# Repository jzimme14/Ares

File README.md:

# Ares
Flight Controller for autonomous drone.

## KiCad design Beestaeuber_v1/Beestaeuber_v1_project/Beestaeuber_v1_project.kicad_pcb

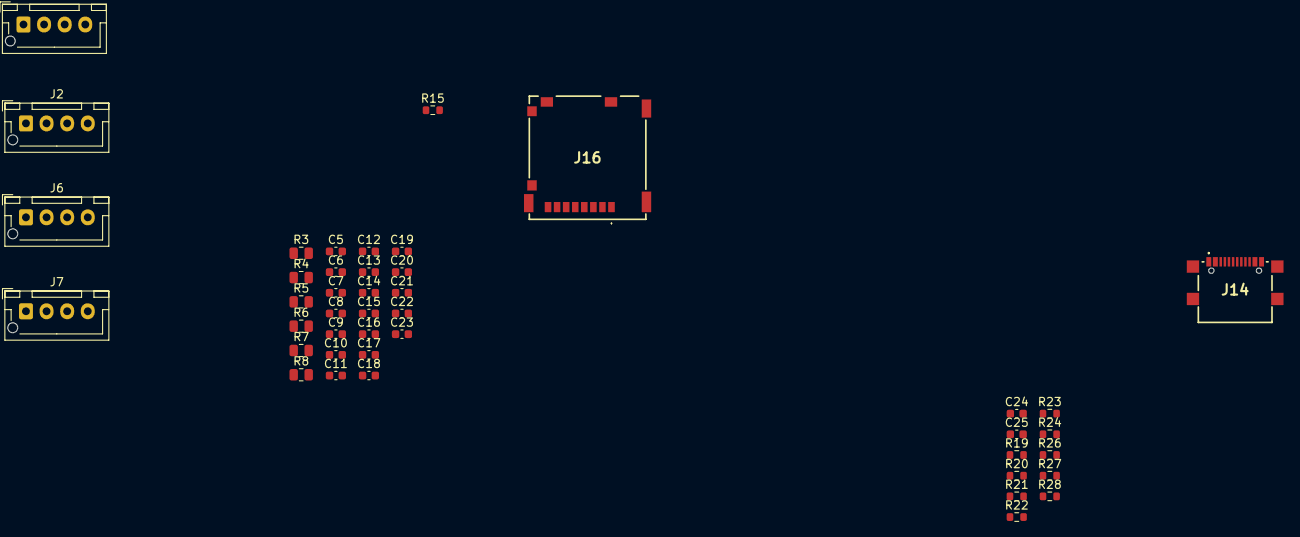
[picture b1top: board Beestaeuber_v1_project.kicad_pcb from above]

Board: 2 copper layers, 43 parts (0 on the bottom side), 20 nets, no tracks yet.

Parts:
C5, C6, C7, C8, C10, C11, C12, C13, C14, C15, C20, C21, C24: 100n; C_0603_1608Metric
C9, C25: 10u; C_0603_1608Metric
C16, C18: 10n; C_0603_1608Metric
C17, C19: 1u; C_0603_1608Metric
C22, C23: 2u2; C_0603_1608Metric
J1: B4B-XH-AM__LF__SN_; JST_XH_B4B-XH-AM_1x04_P2.50mm_Vertical
J2: ELRS_Receiver; JST_XH_B4B-XH-AM_1x04_P2.50mm_Vertical
J6: CAM Connector; JST_XH_B4B-XH-AM_1x04_P2.50mm_Vertical
J7: VTX Output; JST_XH_B4B-XH-AM_1x04_P2.50mm_Vertical
J14: GSB1C41110SSHR
J16: MEM2090-00-145-00-A; MEM20900014500A
R3: 47k; R_0805_2012Metric
R4, R6, R8: 330k; R_0805_2012Metric
R5: 33k; R_0805_2012Metric
R7: 22k; R_0805_2012Metric
R15, R19, R20, R21, R22, R23, R24: 47k; R_0603_1608Metric
R26, R27: 10k; R_0603_1608Metric
R28: 100k; R_0603_1608Metric

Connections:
+3.3VA: C16.1, C17.1, C18.1, C19.1
+3V3: C9.1, C10.1, C11.1, C12.1, C13.1, C14.1, C15.1, C25.1, J16.4 (VDD), R15.1, R19.1, R20.1, R21.1, R22.1, R23.1, R24.1, R26.1, R27.1
+5V: C8.1, J2.3
/D14/A0: C7.1, R7.2, R8.1
/D15/A1: C6.1, R5.2, R6.1
/D20/A6: C5.1, R3.2, R4.1
/Lipo_Cell_1: J1.2, R7.1
/Lipo_Cell_1_2: J1.3, R5.1
/Lipo_Cell_1_2_3: J1.4, R3.1
GND: C5.2, C6.2, C7.2, J1.1, J16.6 (VSS), J16.10 (GROUND_1), J16.11 (GROUND_2), J16.12 (GROUND_3), J16.13 (GROUND_4), J16.14 (GROUND_5), J16.15 (GROUND_6), R4.2, R6.2, R8.2
SDMMC1_CMD: J16.3 (CMD), R24.2
SDMMC1_D0: J16.7 (DAT0), R20.2
SDMMC1_D1: J16.8 (DAT1), R15.2, R19.2
SDMMC1_D2: J16.1 (DAT2), R22.2
SDMMC1_D3: J16.2 (CD/DAT3), R23.2
USB_DN_1: J14.A7 (DN1), J14.B7 (DN2)
USB_DP_1: J14.A6 (DP1), J14.B6 (DP2)
USB_GND_1: C8.2, C9.2, C10.2, C11.2, C12.2, C13.2, C14.2, C15.2, C16.2, C17.2, C18.2, C19.2, C20.2, C21.1, C22.2, C23.2, C24.2, C25.2, J2.4, J14.A1 (GND_1), J14.A12 (GND_2), J14.MP1, J14.MP2, J14.MP3, J14.MP4, R28.2
VBUS_1: C20.1, J14.A4 (VBUS_1), J14.A9 (VBUS_2)
VCAP1: C22.1, C23.1

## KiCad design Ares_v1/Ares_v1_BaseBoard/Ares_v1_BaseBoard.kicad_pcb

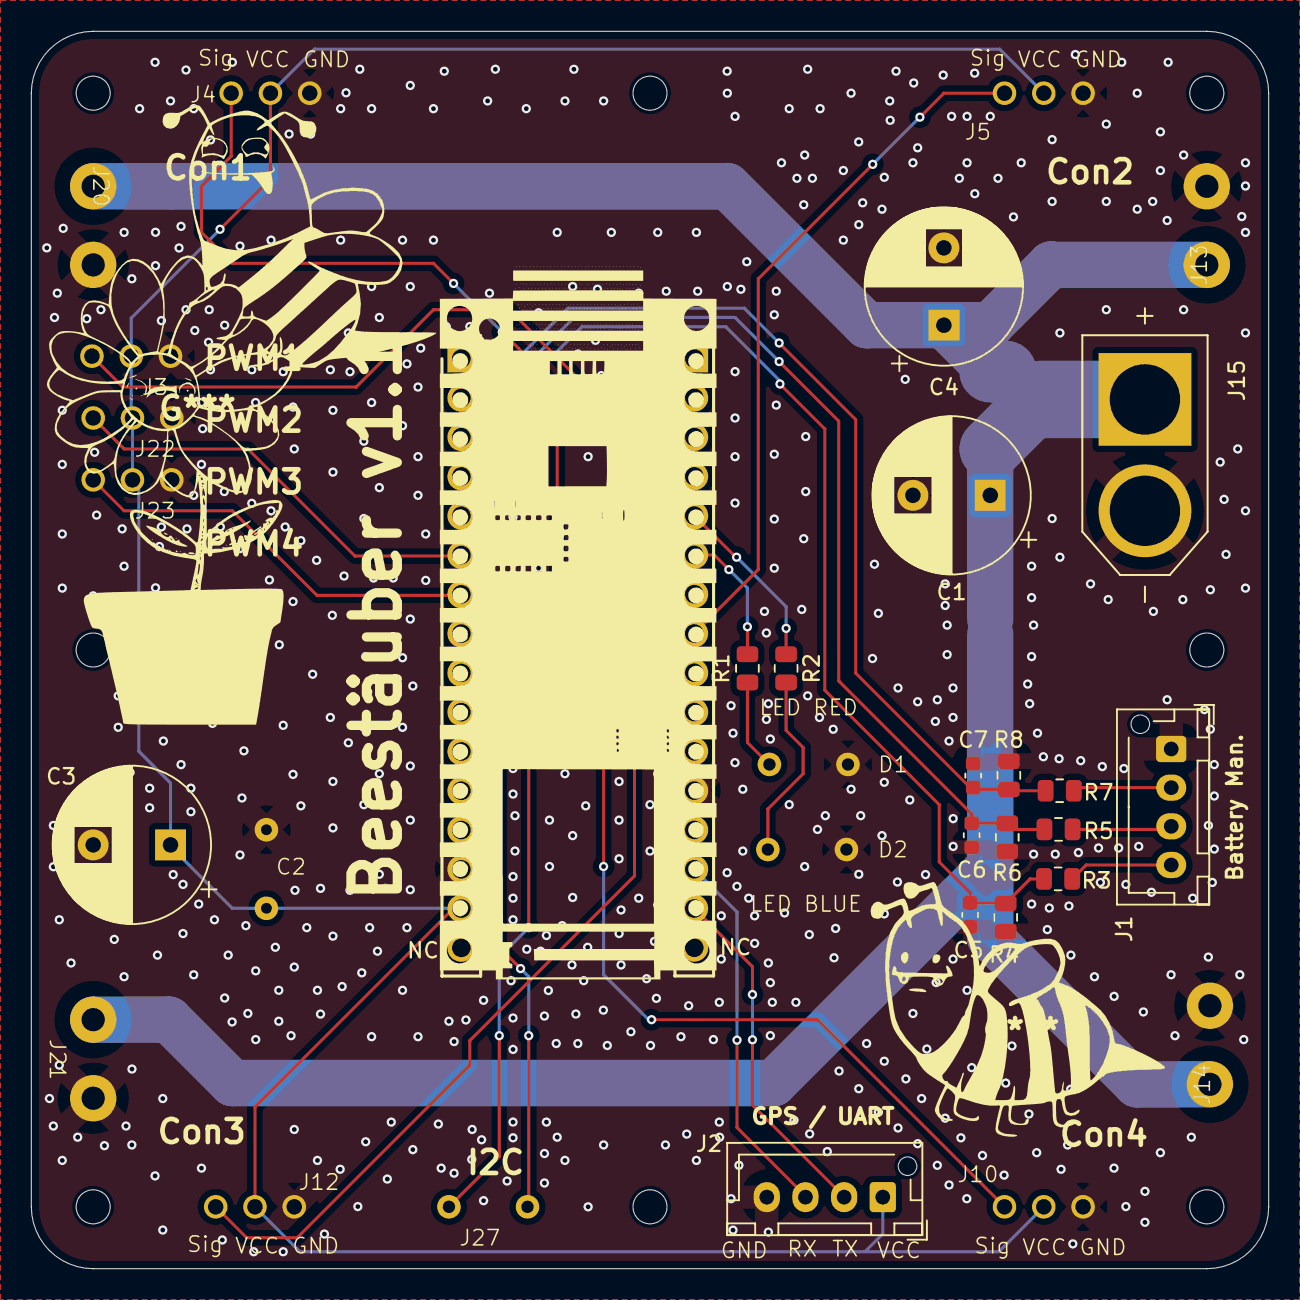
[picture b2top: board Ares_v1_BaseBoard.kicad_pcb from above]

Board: 2 copper layers, 80.0 x 80.0 mm, 33 parts (0 on the bottom side), 24 nets.

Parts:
C1, C3, C4: 1000u; CP_Radial_D10.0mm_P5.00mm
C2: 100n; cap_tht_ceramic
C5, C6, C7: 100n; C_0603_1608Metric
D1: LED/Rot; PowerKlemme
D2: LED/Blau; PowerKlemme
J1, J2: B4B-XH-AM__LF__SN_; JST_XH_B4B-XH-AM_1x04_P2.50mm_Vertical
J3: PWM1/D10; Stiftleiste3Pin
J4: PWM Connector 1; Stiftleiste3Pin
J5: PWM Connector 2; Stiftleiste3Pin
J10: PWM Connector 4; Stiftleiste3Pin
J12: PWM Connector 3; Stiftleiste3Pin
J13: Motor Power Connector 2; PowerKlemme
J14: Motor Power Connector 4; PowerKlemme
J15: XT60-M; AMASS_XT60-M
J20: Motor Power Connector 1; PowerKlemme
J21: Motor Power Connector 3; PowerKlemme
J22: PWM2/D16; Stiftleiste3Pin
J23: PWM3/D17; Stiftleiste3Pin
J27: I2C_Conn; PowerKlemme
R1: 220; R_0805_2012Metric
R2: 0; R_0805_2012Metric
R3: 47k; R_0805_2012Metric
R4, R6, R8: 330k; R_0805_2012Metric
R5: 33k; R_0805_2012Metric
R7: 22k; R_0805_2012Metric
U1: ABX00027; ArduinoNano33IOT_Stiftleiste

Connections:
+5V: C2.1, C3.1, J2.1, J3.2, J4.2, J5.2, J10.2, J12.2, J22.2, J23.2, U1.15 (VIN)
+12V: C1.1, C4.1, J13.1, J14.1, J15.P (POS), J20.1, J21.1
/D4/PWM: J4.1, U1.22 (D4)
/D5/PWM: J5.1, U1.23 (D5/PWM)
/D6/PWM: J12.1, U1.24 (D6/PWM)
/D7/LED1: R1.1, U1.25 (D7)
/D8/LED2: R2.1, U1.26 (D8)
/D9/PWM: J10.1, U1.27 (D9/PWM)
/D10/PWM: J3.1, U1.28 (D10/PWM)
/D14/A0: C7.1, R7.2, R8.1, U1.4 (A0/DAC0)
/D15/A1: C6.1, R5.2, R6.1, U1.5 (A1)
/D16/PWM: J22.1, U1.6 (A2)
/D17/PWM: J23.1, U1.7 (A3)
/D18/SDA: J27.1, U1.8 (A4/SDA)
/D19/SCL: J27.2, U1.9 (A5/SCL)
/D20/A6: C5.1, R3.2, R4.1, U1.10 (A6)
/Lipo_Cell_1: J1.2, R7.1
/Lipo_Cell_1_2: J1.3, R5.1
/Lipo_Cell_1_2_3: J1.4, R3.1
/UART_RX: J2.3, U1.17 (RX)
/UART_TX: J2.2, U1.16 (TX)
GND: C1.2, C2.2, C3.2, C4.2, C5.2, C6.2, C7.2, D1.1 (K), D2.1 (K), J1.1, J2.4, J3.3, J4.3, J5.3, J10.3, J12.3, J13.2, J14.2, J15.N (NEG), J20.2, J21.2, J22.3, J23.3, R4.2, R6.2, R8.2, U1.14 (GND)
unnamed: D1.2 (A), R1.2
unnamed: D2.2 (A), R2.2

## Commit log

2024-05-15 printfile added
2024-05-15 added open source 3d-printing drone design as prototype. especially for FC testing
2024-05-17 pid controller in python implementation
2024-05-19 added low pass filter implementation and tools
2024-05-21 implemented low pass filter using backward euler to discretise calculated differential equation
